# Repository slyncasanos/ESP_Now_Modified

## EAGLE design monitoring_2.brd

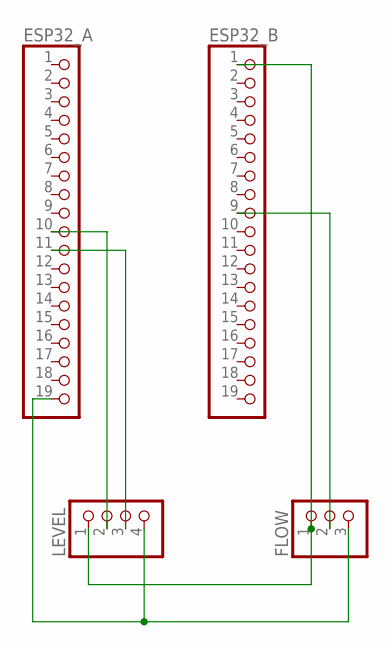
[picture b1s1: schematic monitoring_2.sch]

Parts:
ESP32_A, ESP32_B: PINHD-1X19; 1X19
FLOW: PINHD-1X3; 1X03
LEVEL: PINHD-1X4; 1X04

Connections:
unnamed: ESP32_B.1, FLOW.1, LEVEL.1
unnamed: ESP32_A.19, FLOW.3, LEVEL.4
unnamed: ESP32_A.10, LEVEL.2
unnamed: ESP32_A.11, LEVEL.3
unnamed: ESP32_B.9, FLOW.2

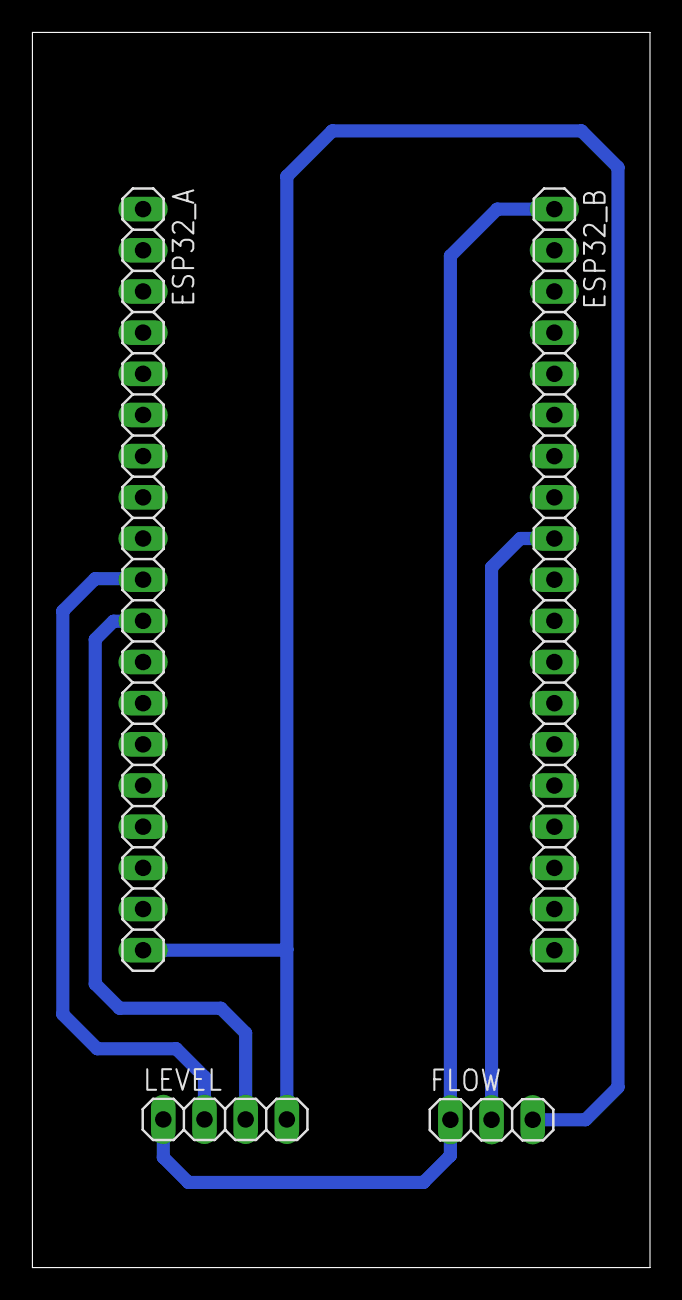
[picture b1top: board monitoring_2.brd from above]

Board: 2 copper layers, 38.1 x 76.2 mm, 4 parts (0 on the bottom side), 5 nets.

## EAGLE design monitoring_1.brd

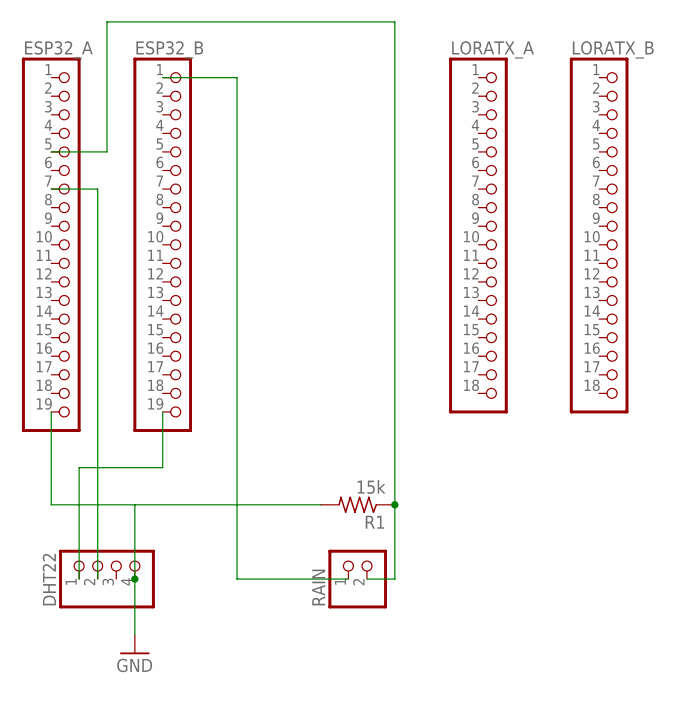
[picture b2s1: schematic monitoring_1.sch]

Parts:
DHT22: PINHD-1X4; 1X04
ESP32_A, ESP32_B: PINHD-1X19; 1X19
LORATX_A: PINHD-1X18; 1X18
LORATX_B: PINHD-1X18; 1X18
R1: 15k; 0204/7
RAIN: PINHD-1X2; 1X02

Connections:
GND: DHT22.4, ESP32_A.19, R1.2
unnamed: ESP32_A.5, R1.1, RAIN.2
unnamed: DHT22.2, ESP32_A.7
unnamed: DHT22.1, ESP32_B.19
unnamed: ESP32_B.1, RAIN.1

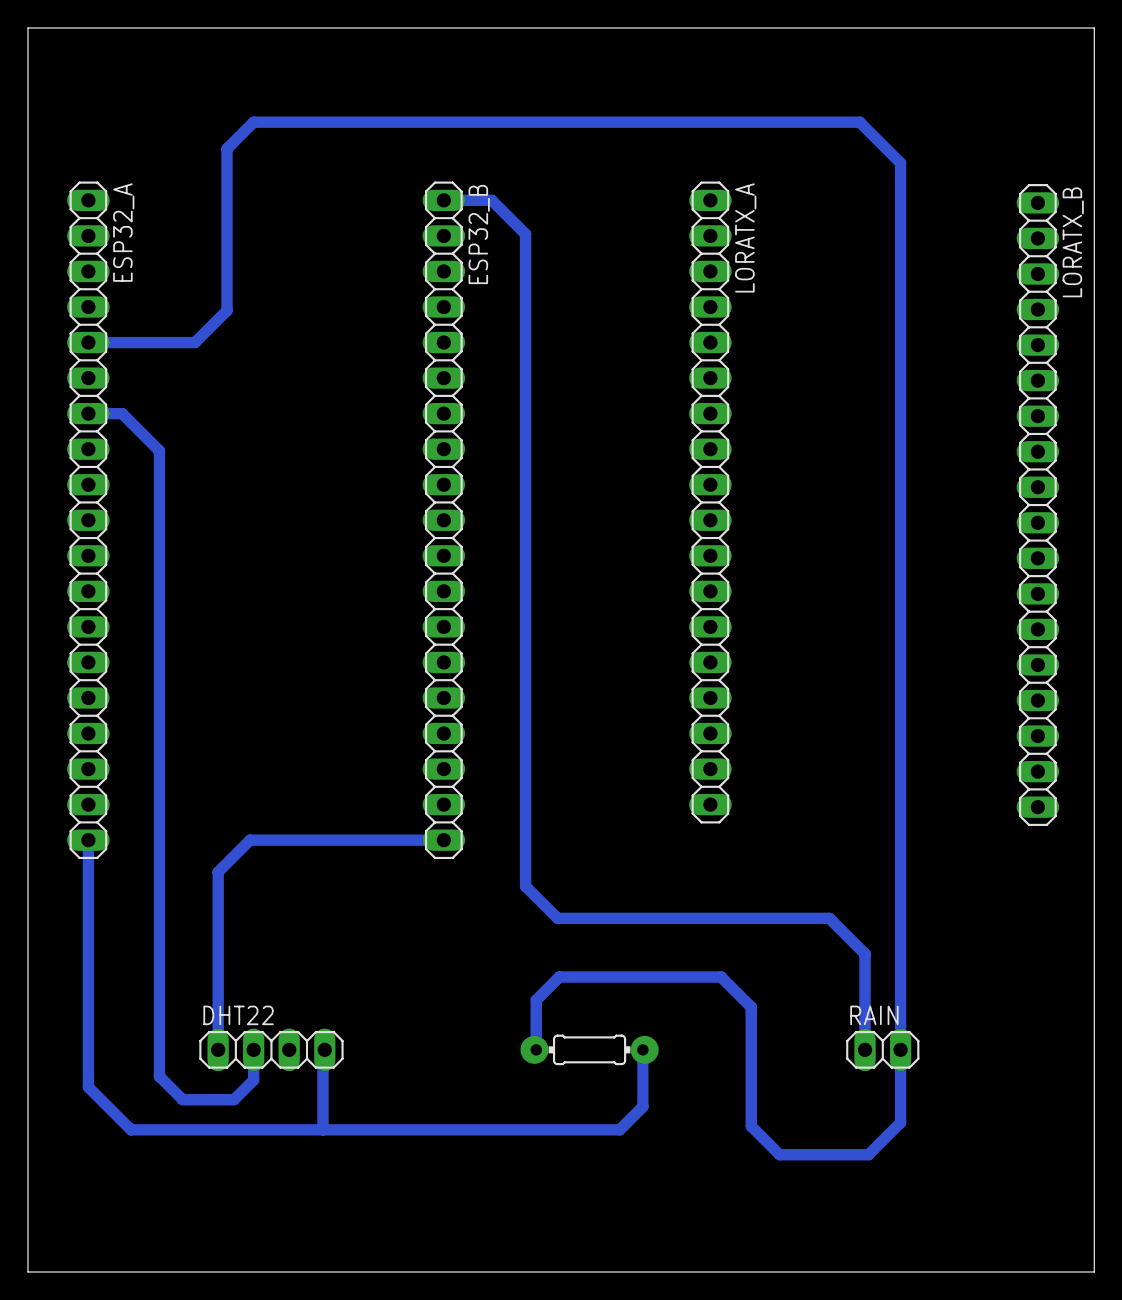
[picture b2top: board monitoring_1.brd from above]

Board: 2 copper layers, 76.2 x 88.9 mm, 7 parts (0 on the bottom side), 5 nets.
